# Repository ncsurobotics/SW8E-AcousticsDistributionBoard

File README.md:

# SW8E-AcousticsDistributionBoard

1-4 Ch power distribution for acoustics single channel boards used on SW8.

- PCB is designed in Altium. Project is in [AltiumPCB](./AltiumPCB)

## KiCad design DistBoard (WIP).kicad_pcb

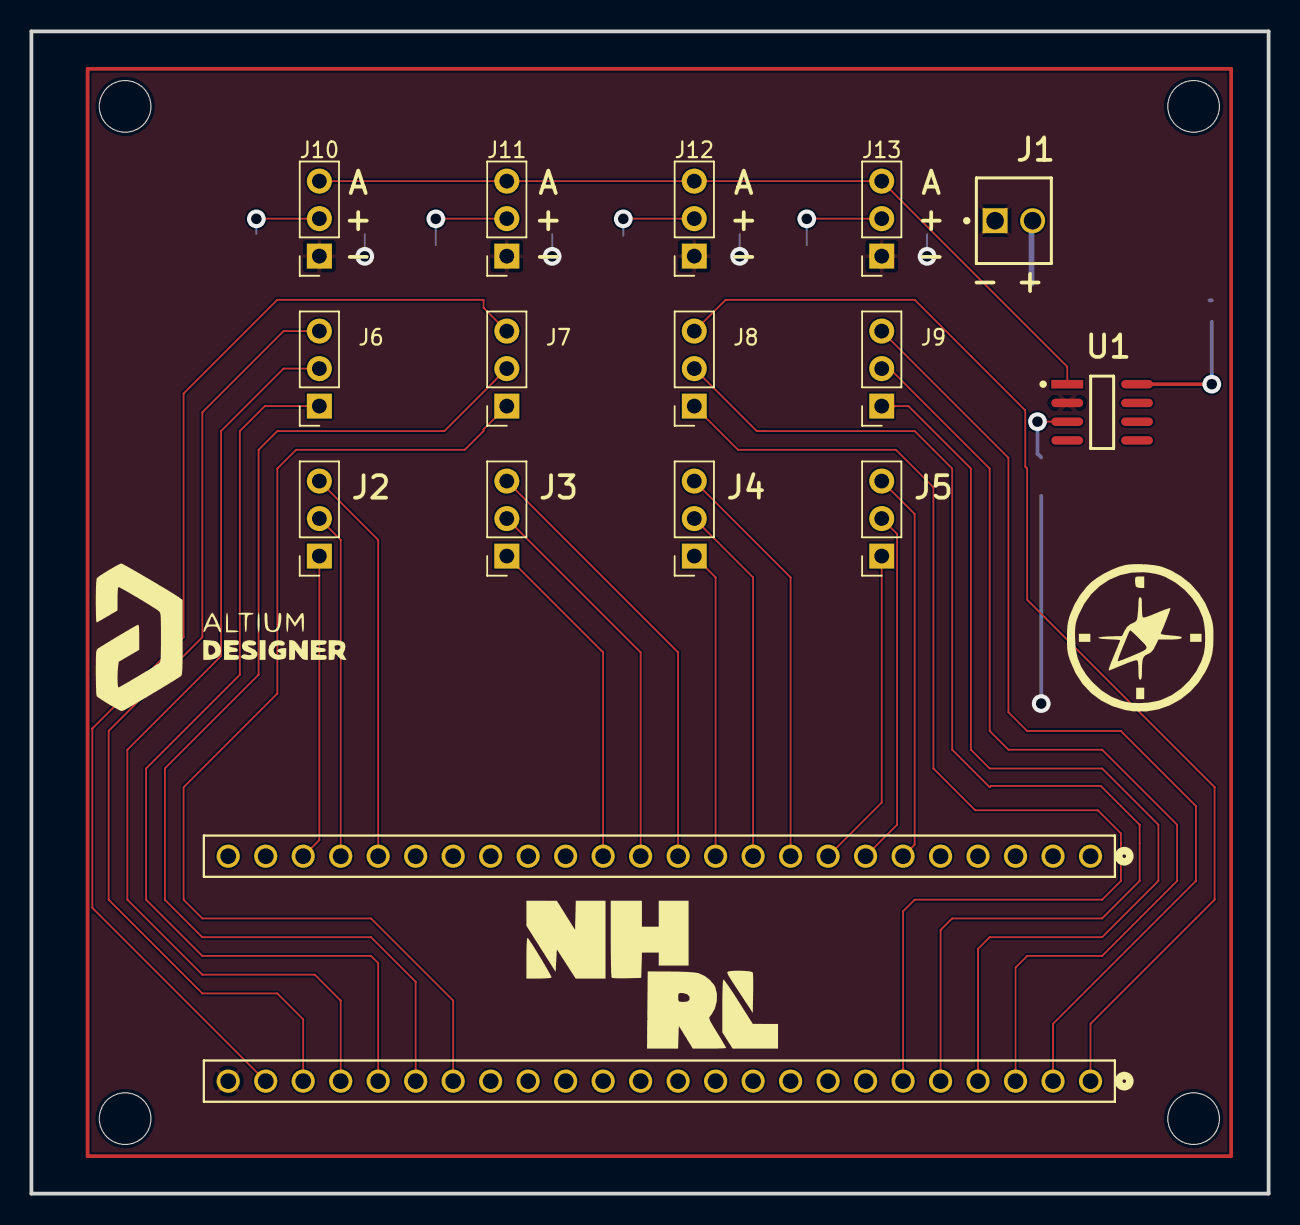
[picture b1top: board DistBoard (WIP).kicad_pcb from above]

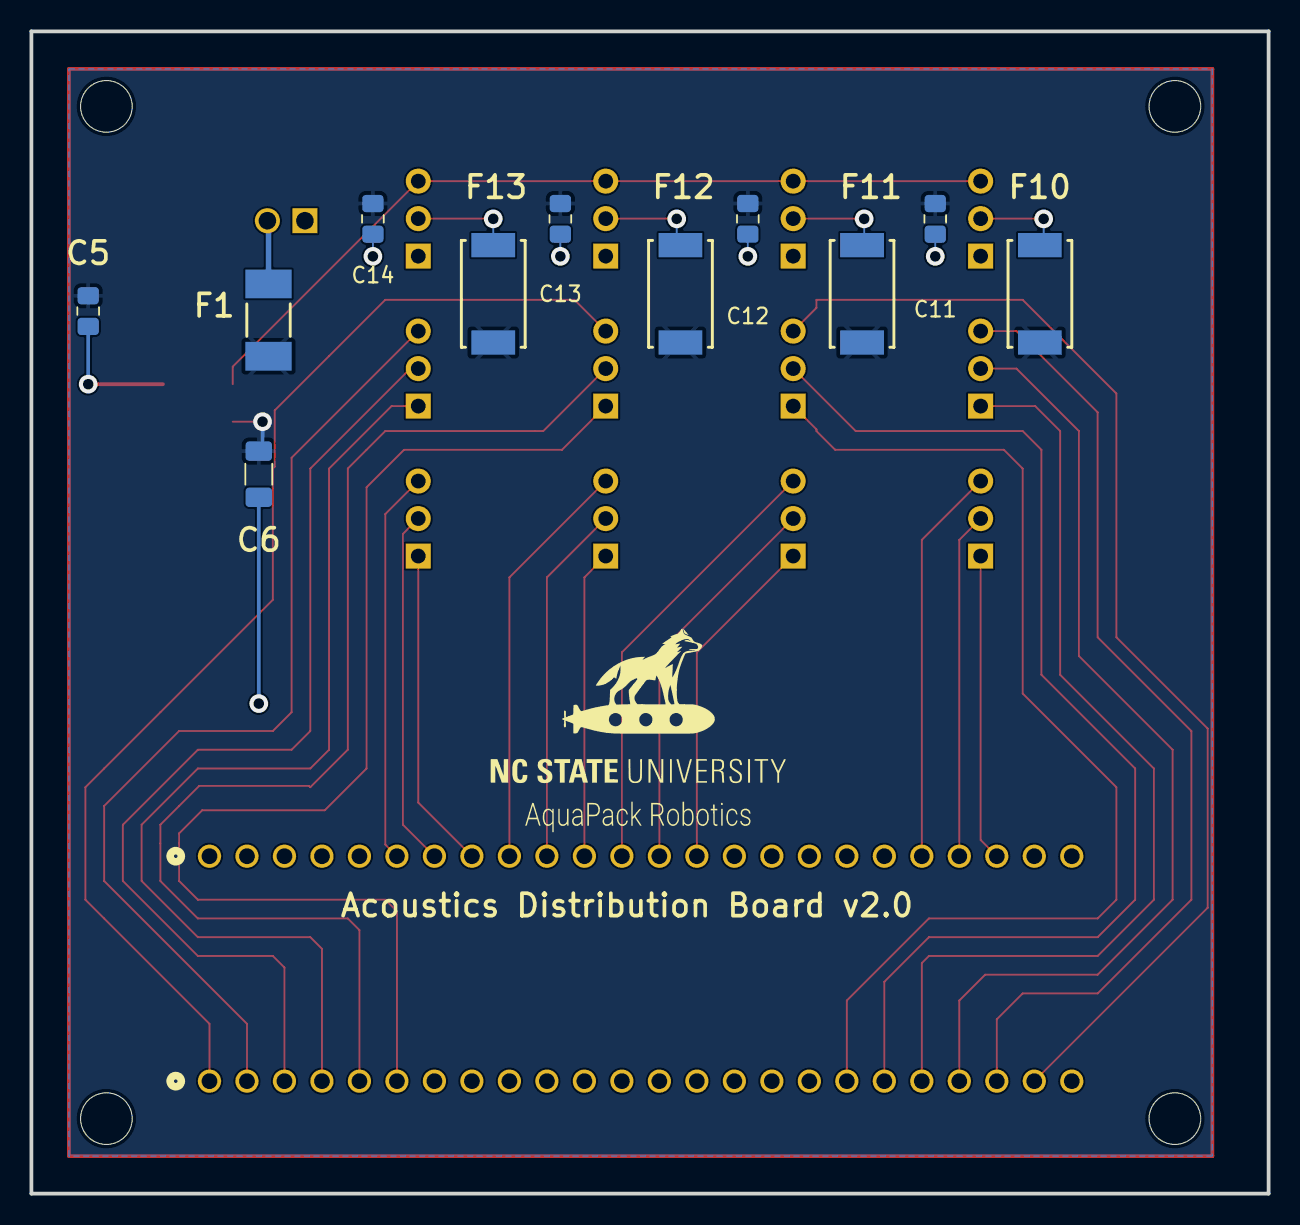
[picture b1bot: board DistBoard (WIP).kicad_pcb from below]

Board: 2 copper layers, 83.8 x 78.7 mm, 27 parts (11 on the bottom side), 33 nets.

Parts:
C5: 100nF; C_0805_2012Metric_Pad1.18x1.45mm_HandSolder
C6: 1uF; C_1206_3216Metric_Pad1.33x1.80mm_HandSolder
C11, C12, C13, C14: 1uF; C_0805_2012Metric_Pad1.18x1.45mm_HandSolder
F1: 1.5A; FP-0452-MFG
F10, F11, F12, F13: 0.25A; LFUS-459_V
J1: 22-27-2021; MOLX-22-27-2021_V
J2, J3, J4, J5, J6, J7, J8, J9, J10, J11, J12, J13: Conn_01x03; PinSocket_1x03_P2.54mm_Vertical
J14, J15: PPTC241LFBN-RC; CONN24_PPTC241LFBN-RC_SUL
U1: TLE2426CDR; FP-D0008A-IPC_B

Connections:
+5V: C5.2, C6.1, C11.2, C12.2, C13.2, C14.2, F1.2, F10.1, F11.1, F12.1, F13.1, U1.3 (IN)
/AGND: J10.3, J11.3, J12.3, J13.3, U1.1 (OUT)
/J2 (CLK): J2.2, J14.21
/J2 (CS): J2.3, J14.20
/J2 (DOUT): J2.1, J14.22
/J3 (CLK): J3.2, J14.13
/J3 (CS): J3.3, J14.12
/J3 (DOUT): J3.1, J14.14
/J4 (CLK): J4.2, J14.10
/J4 (CS): J4.3, J14.9
/J4 (DOUT): J4.1, J14.11
/J5 (CLK): J5.2, J14.7
/J5 (CS): J5.3, J14.6
/J5 (DOUT): J5.1, J14.8
/J6 (G0 OUT): J6.1, J15.20
/J6 (G1 OUT): J6.2, J15.21
/J6 (G2 OUT): J6.3, J15.22
/J7 (G0 OUT): J7.1, J15.18
/J7 (G1 OUT): J7.2, J15.19
/J7 (G2 OUT): J7.3, J15.23
/J8 (G0 OUT): J8.1, J15.6
/J8 (G1 OUT): J8.2, J15.5
/J8 (G2 OUT): J8.3, J15.1
/J9 (G0 OUT): J9.1, J15.4
/J9 (G1 OUT): J9.2, J15.3
/J9 (G2 OUT): J9.3, J15.2
/NR: C5.1, U1.8 (NOISE_REDUCTION)
GND: C6.2, C11.1, C12.1, C13.1, C14.1, J1.1, J10.1, J11.1, J12.1, J13.1, J15.24, U1.2 (COMMON)
unnamed: F1.1, J1.2
unnamed: F10.2, J10.2
unnamed: F11.2, J11.2
unnamed: F12.2, J12.2
unnamed: F13.2, J13.2

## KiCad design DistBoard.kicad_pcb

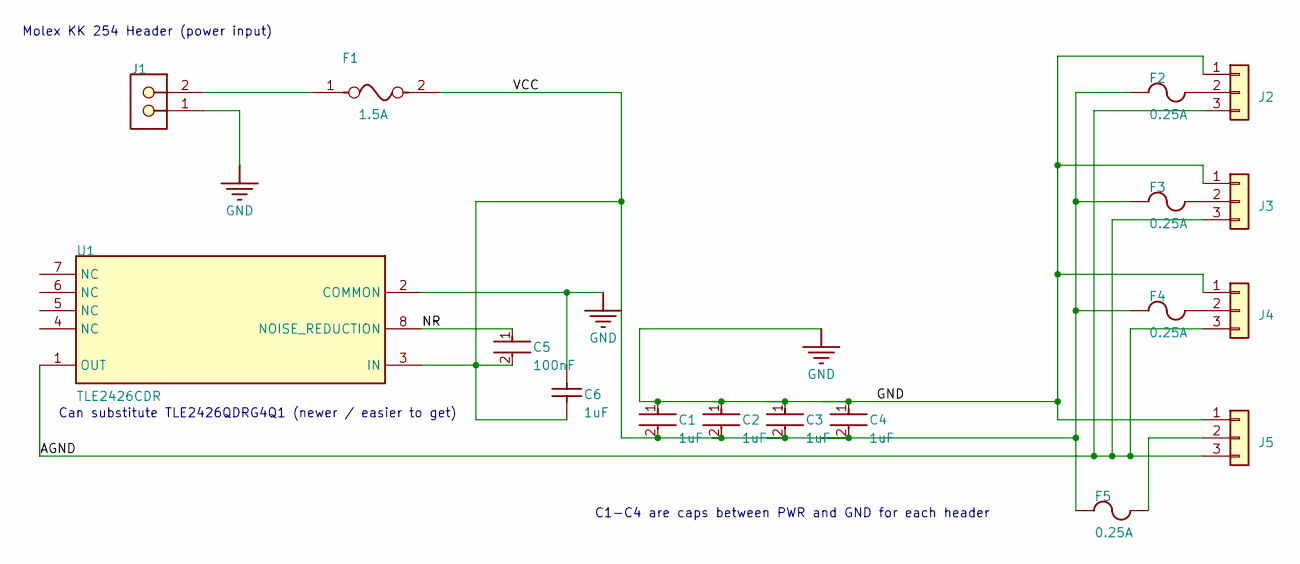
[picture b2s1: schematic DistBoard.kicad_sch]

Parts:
C1, C2, C3, C4: 1uF; C_0805_2012Metric_Pad1.18x1.45mm_HandSolder; Part Number GCJ21BR71H105KA01L
C5: 100nF; C_0805_2012Metric_Pad1.18x1.45mm_HandSolder; Part Number GCD21BR71H104KA01L
C6: 1uF; C_1206_3216Metric_Pad1.33x1.80mm_HandSolder; Part Number C1206C105K5RACTU
F1: 1.5A; FP-0452-MFG; Part Number 045201.5MRL
F2, F3, F4, F5: 0.25A; LFUS-459_V; Part Number 0459.250UR
J1: 22-27-2021; MOLX-22-27-2021_V; Part Number 22-27-2021
J2, J3, J4, J5: Conn_01x03; PinSocket_1x03_P2.54mm_Vertical
U1: TLE2426CDR; FP-D0008A-IPC_B; Part Number TLE2426CDR

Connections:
/AGND: J2.3, J3.3, J4.3, J5.3, U1.1 (OUT)
/NR: C5.1, U1.8 (NOISE_REDUCTION)
/VCC: C1.2, C2.2, C3.2, C4.2, C5.2, C6.1, F1.2, F2.1, F3.1, F4.1, F5.1, U1.3 (IN)
GND: C1.1, C2.1, C3.1, C4.1, C6.2, J1.1, J2.1, J3.1, J4.1, J5.1, U1.2 (COMMON)
unnamed: F1.1, J1.2
unnamed: F2.2, J2.2
unnamed: F3.2, J3.2
unnamed: F4.2, J4.2
unnamed: F5.2, J5.2

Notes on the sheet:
C1-C4 are caps between PWR and GND for each header
Can substitute TLE2426QDRG4Q1 (newer / easier to get)
Molex KK 254 Header (power input)

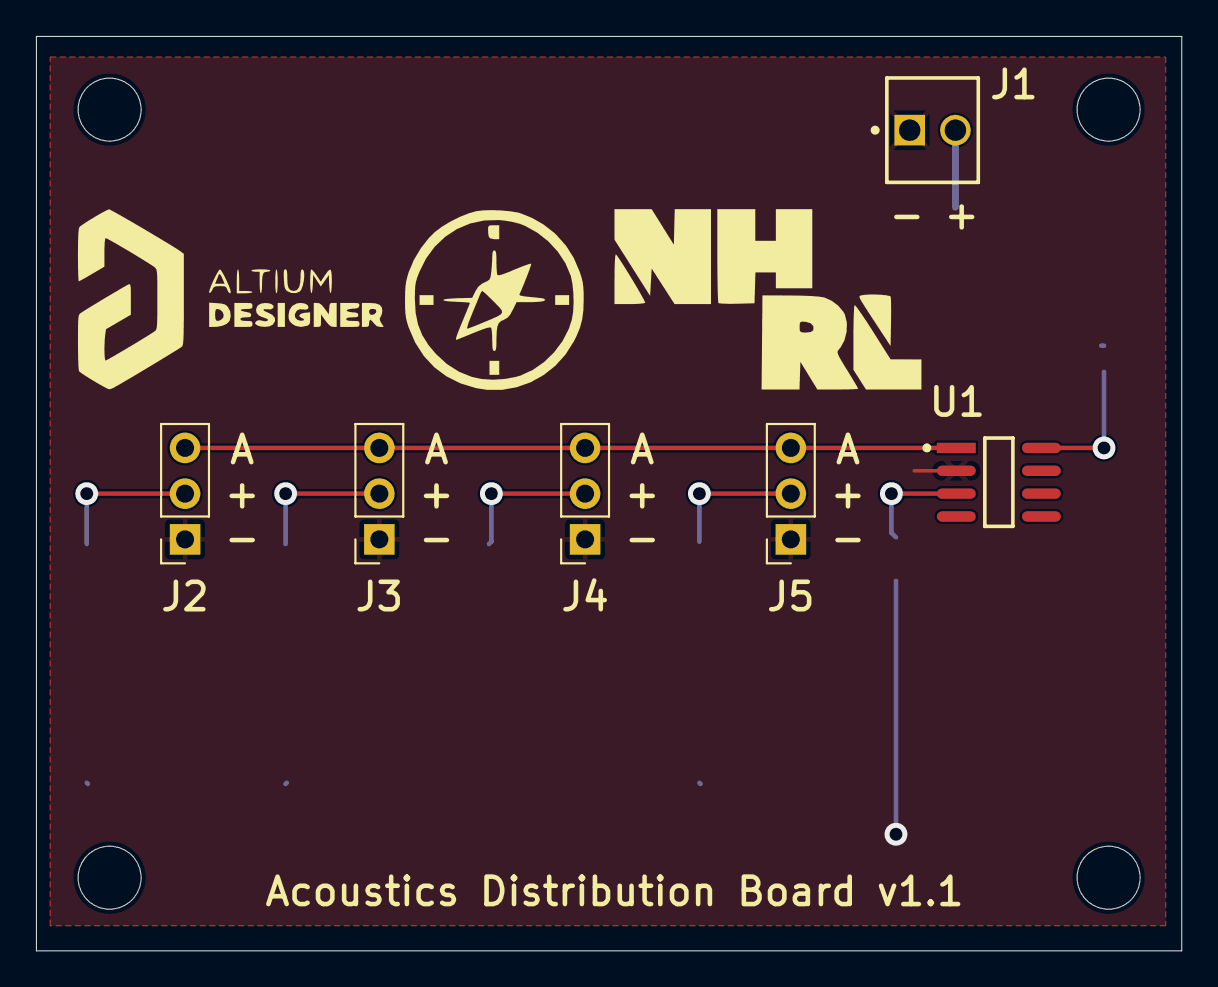
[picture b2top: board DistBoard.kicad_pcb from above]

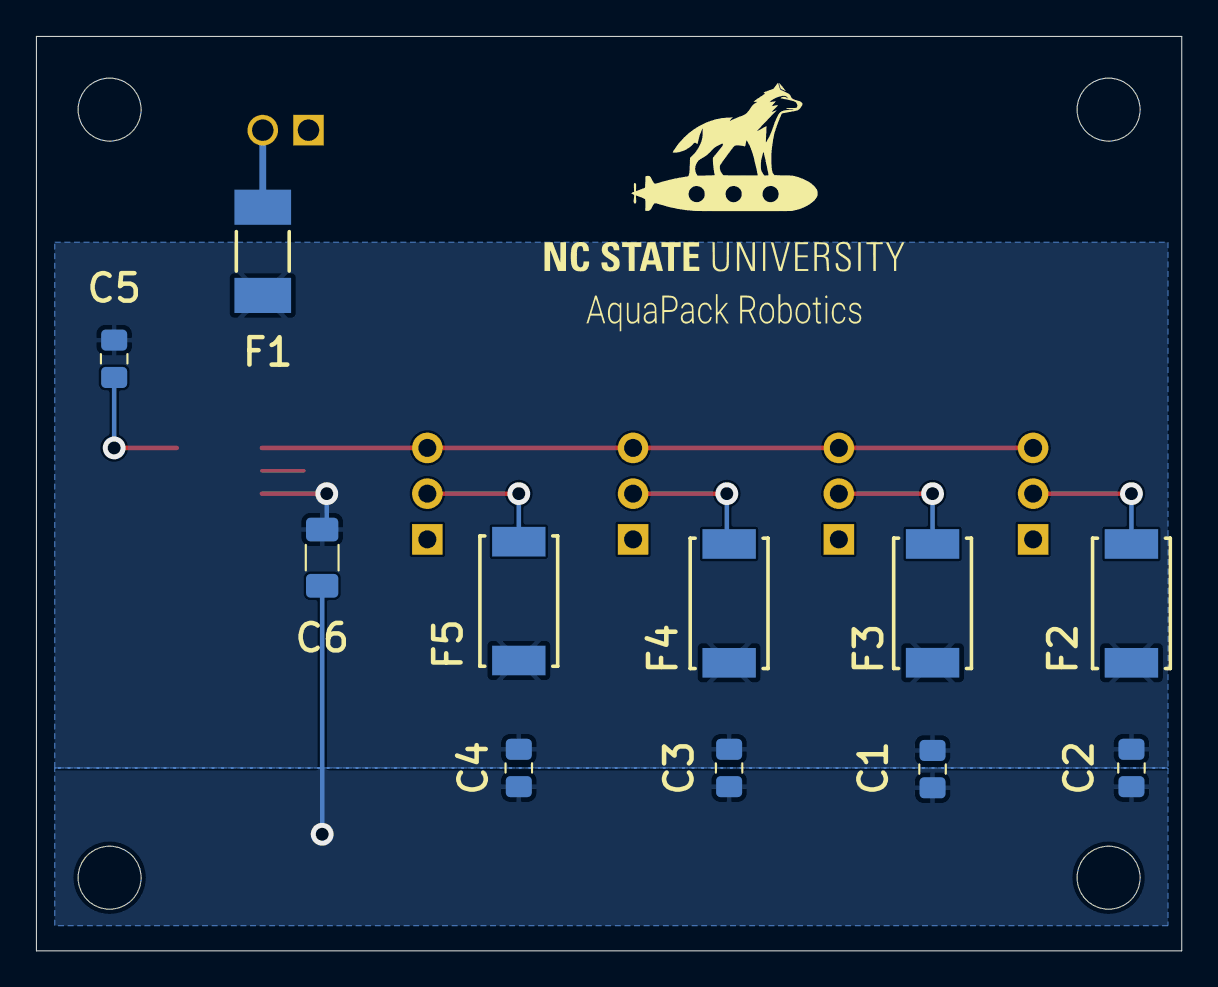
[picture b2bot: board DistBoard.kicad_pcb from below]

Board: 2 copper layers, 63.6 x 50.8 mm, 17 parts (11 on the bottom side), 9 nets.

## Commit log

2022-09-15 Initial setup completed, repo ready for use
2022-09-19 Created Altium Project files
2022-09-20 Added AGND to schematic and created PCB file
2022-09-29 First version of schematic, needs revision review
2022-09-29 Got rid of some caps and reorganized input header
2022-09-29 Removed the 2 amp fuse, replaced with a single 1 amp fuse
2022-10-12 Laying out PCB. Headers have to be lined up
2022-10-14 Laid out PCB, need to route traces
2022-10-14 Finished first edition of board. Ready to review and revise
2022-10-14 Minor changes for looks
2022-10-17 Added text to indicate the pins for the headers
2022-10-18 Changed some routing
2022-10-19 Created BoM
2022-10-22 Added measurement to PCB. Edited BoM
2022-10-22 Add alternate part comment for agnd chip
2022-10-27 Added revisions from PCB review. More fuses, polygons, and reorganized board
2022-10-31 Added mounting holes
2022-11-01 updated BOM, changed C6
2022-11-09 Finishing BOM
2023-01-17 Fix mounting hole sizes
2023-01-17 Add correct design rules to project
2023-01-17 Added silkscreen logos
2023-04-08 Flattened unnecessarily deep repo structure
2023-04-10 Everything but step 8 in the conversion doc completed
2023-04-11 Converted Altium to KiCad actually did it right this time
2023-04-18 Add kicad gitignore
2023-04-18 Remove altium files
2023-04-18 Import board settings
2023-04-18 Fix mounting holes
2023-04-18 Fix silkscreen sizes
2023-04-18 Swap to through hole headers
2023-04-18 Swap to socket headers and fix drc violations
2023-04-18 Add logos
2023-04-18 Schematic and BOM cleanup
2023-04-18 Change capacitor footprints
2023-04-18 Move some silkscreen
2023-04-18 Import default sizes from template
2023-04-18 Fix schematic footprints not matching PCB
2023-07-04 Remove imported symbol table fiends
2023-07-04 Update board settings from template
2023-07-04 Mark mounting holes as 'not in schematic'
2023-11-18 intial design of v2.0 carrying FPGA module.
2023-11-21 Changed PCB to correct spacing on all headers and corrected routes to FPGA headers. Changed schematic to include net labels instead of physical wires and corrected routing from single channel boards 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
2023-11-21 fixed readability issues.
2024-01-09 improved readability.
